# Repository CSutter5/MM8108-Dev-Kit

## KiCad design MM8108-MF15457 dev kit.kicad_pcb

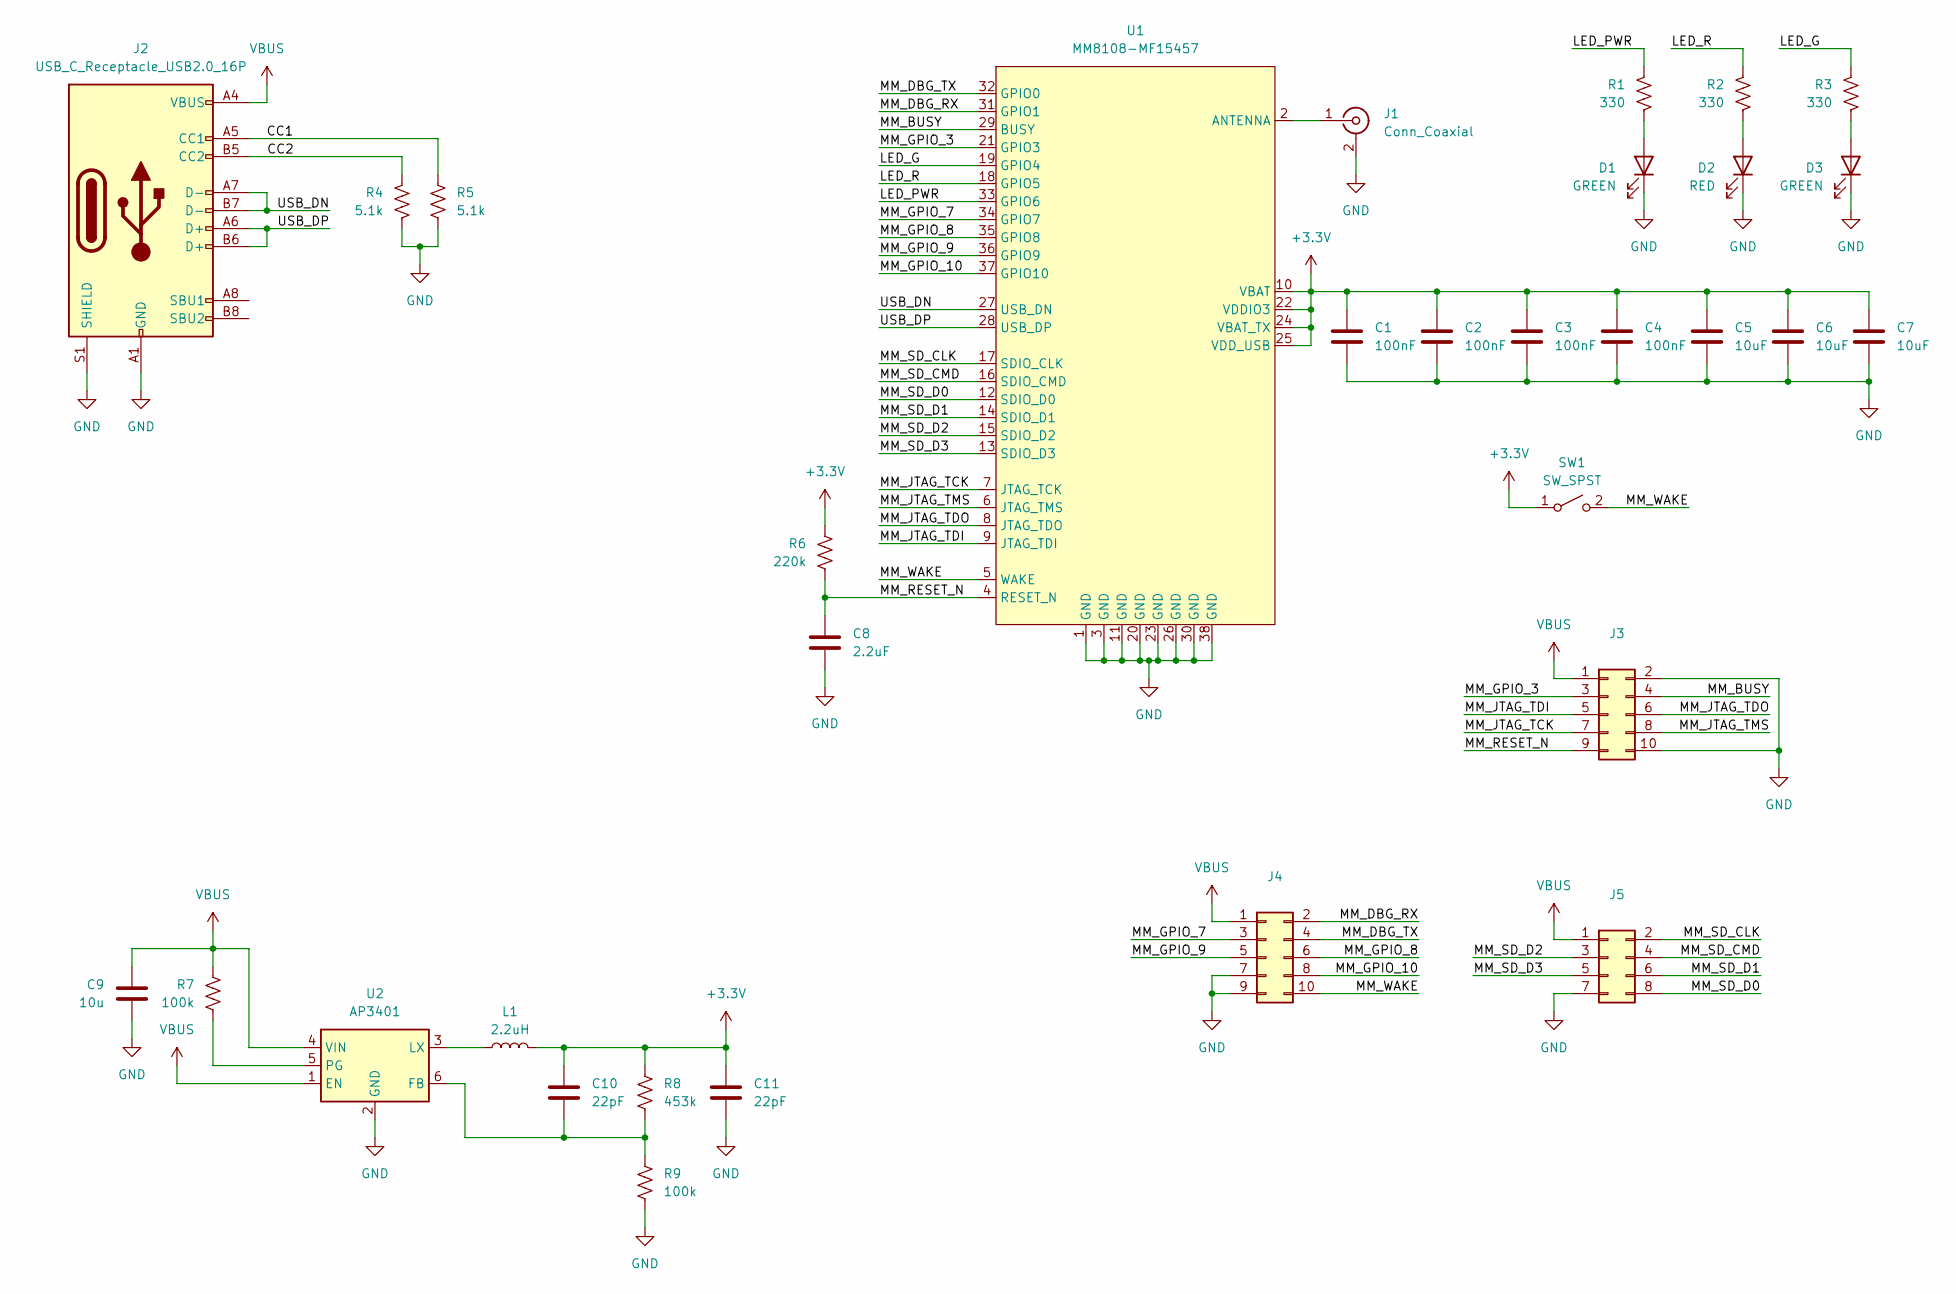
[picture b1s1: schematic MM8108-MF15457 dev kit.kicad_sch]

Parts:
C1, C2, C3, C4: 100nF; C_0603_1608Metric_Pad1.08x0.95mm_HandSolder
C5, C6, C7: 10uF; C_0603_1608Metric_Pad1.08x0.95mm_HandSolder
C8: 2.2uF; C_0603_1608Metric_Pad1.08x0.95mm_HandSolder
C9: 10u; C_0603_1608Metric_Pad1.08x0.95mm_HandSolder
C10, C11: 22pF; C_0603_1608Metric_Pad1.08x0.95mm_HandSolder
D1, D3: GREEN; D_0603_1608Metric_Pad1.05x0.95mm_HandSolder
D2: RED; D_0603_1608Metric_Pad1.05x0.95mm_HandSolder
J1: Conn_Coaxial; SMA_Samtec_SMA-J-P-H-ST-EM1_EdgeMount
J2: USB_C_Receptacle_USB2.0_16P; USB_C_Receptacle_GCT_USB4105-xx-A_16P_TopMnt_Horizontal
J3, J4: Conn_02x05_Odd_Even; PinSocket_2x05_P2.54mm_Vertical
J5: Conn_02x04_Odd_Even; PinHeader_2x04_P2.54mm_Vertical
L1: 2.2uH; L_0805_2012Metric_Pad1.05x1.20mm_HandSolder
R1, R2, R3: 330; R_0603_1608Metric_Pad0.98x0.95mm_HandSolder
R4, R5: 5.1k; R_0603_1608Metric_Pad0.98x0.95mm_HandSolder
R6: 220k; R_0603_1608Metric_Pad0.98x0.95mm_HandSolder
R7, R9: 100k; R_0603_1608Metric_Pad0.98x0.95mm_HandSolder
R8: 453k; R_0603_1608Metric_Pad0.98x0.95mm_HandSolder
SW1: SW_SPST; SW_Tactile_SPST_NO_Straight_CK_PTS636Sx25SMTRLFS
U1: MM8108-MF15457; MF15457
U2: AP3401; TSOT-23-6_HandSoldering

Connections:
+3.3V: C1.1, C2.1, C3.1, C4.1, C5.1, C6.1, C7.1, C10.1, C11.1, L1.2, R6.1, R8.1, SW1.1 (A), U1.10 (VBAT), U1.22 (VDDIO3), U1.24 (VBAT_TX), U1.25 (VDD_USB)
/CC1: J2.A5 (CC1), R5.1
/CC2: J2.B5 (CC2), R4.1
/LED_G: R3.1, U1.19 (GPIO4)
/LED_PWR: R1.1, U1.33 (GPIO6)
/LED_R: R2.1, U1.18 (GPIO5)
/MM_BUSY: J3.4, U1.29 (BUSY)
/MM_DBG_RX: J4.2, U1.31 (GPIO1)
/MM_DBG_TX: J4.4, U1.32 (GPIO0)
/MM_GPIO_3: J3.3, U1.21 (GPIO3)
/MM_GPIO_7: J4.3, U1.34 (GPIO7)
/MM_GPIO_8: J4.6, U1.35 (GPIO8)
/MM_GPIO_9: J4.5, U1.36 (GPIO9)
/MM_GPIO_10: J4.8, U1.37 (GPIO10)
/MM_JTAG_TCK: J3.7, U1.7 (JTAG_TCK)
/MM_JTAG_TDI: J3.5, U1.9 (JTAG_TDI)
/MM_JTAG_TDO: J3.6, U1.8 (JTAG_TDO)
/MM_JTAG_TMS: J3.8, U1.6 (JTAG_TMS)
/MM_RESET_N: C8.1, J3.9, R6.2, U1.4 (RESET_N)
/MM_SD_CLK: J5.2, U1.17 (SDIO_CLK)
/MM_SD_CMD: J5.4, U1.16 (SDIO_CMD)
/MM_SD_D0: J5.8, U1.12 (SDIO_D0)
/MM_SD_D1: J5.6, U1.14 (SDIO_D1)
/MM_SD_D2: J5.3, U1.15 (SDIO_D2)
/MM_SD_D3: J5.5, U1.13 (SDIO_D3)
/MM_WAKE: J4.10, SW1.2 (B), U1.5 (WAKE)
/USB_DN: J2.A7 (D-), J2.B7 (D-), U1.27 (USB_DN)
/USB_DP: J2.A6 (D+), J2.B6 (D+), U1.28 (USB_DP)
GND: C1.2, C2.2, C3.2, C4.2, C5.2, C6.2, C7.2, C8.2, C9.2, C11.2, D1.1 (K), D2.1 (K), D3.1 (K), J1.2 (Ext), J2.A1 (GND), J2.A12 (GND), J2.B1 (GND), J2.B12 (GND), J2.S1 (SHIELD), J3.2, J3.10, J4.7, J4.9, J5.7, R4.2, R5.2, R9.2, U1.1 (GND), U1.3 (GND), U1.11 (GND), U1.20 (GND), U1.23 (GND), U1.26 (GND), U1.30 (GND), U1.38 (GND), U2.2 (GND)
unnamed: D1.2 (A), R1.2
unnamed: D2.2 (A), R2.2
unnamed: D3.2 (A), R3.2
unnamed: J1.1 (In), U1.2 (ANTENNA)
unnamed: C10.2, R8.2, R9.1, U2.6 (FB)
unnamed: L1.1, U2.3 (LX)
unnamed: R7.2, U2.5 (PG)
VBUS: C9.1, J2.A4 (VBUS), J2.A9 (VBUS), J2.B4 (VBUS), J2.B9 (VBUS), J3.1, J4.1, J5.1, R7.1, U2.1 (EN), U2.4 (VIN)

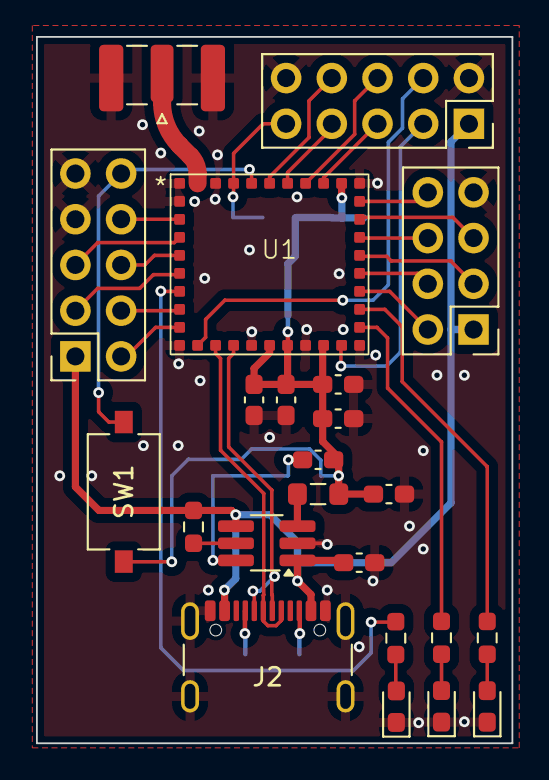
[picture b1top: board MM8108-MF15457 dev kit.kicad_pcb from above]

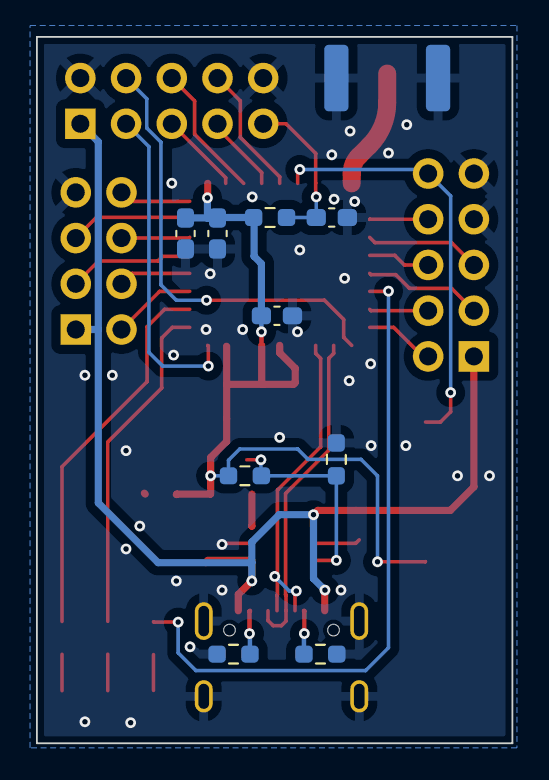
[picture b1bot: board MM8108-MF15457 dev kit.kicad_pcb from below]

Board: 2 copper layers, 26.4 x 39.2 mm, 32 parts (9 on the bottom side), 37 nets.

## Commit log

2026-02-19 Uploaded basic KiCad design
2026-02-19 Renamed KiCad project files
